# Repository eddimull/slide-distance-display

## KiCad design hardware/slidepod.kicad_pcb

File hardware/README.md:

# SlidePod: wireless trombone slide sensor

A single clip-on pod for the stationary inner slide. It measures slide extension with a
VL53L1X time-of-flight sensor and pitch with a piezo contact pickup. It sends position,
pitch and partial over BLE to the Flutter app. There is no screen and no wire to the bell.

## Mechanical constraint that shapes the board

The VL53L1X emits **perpendicular to the PCB**. For the beam to run down the slide, the
board stands as a thin "fin" perpendicular to the slide tubes:

```
        side view (slide runs left → right)

            ┌──┐  ← antenna end (top, away from brass)
            │  │
     PCB →  │  │──►  ToF beam toward the reflector tab on the outer handle brace
   (fin)    │  │
            │▓▓│  ← battery behind the board
     ═══════╧══╧═════════ inner slide tube (clamp + piezo at bottom)
```

- The ToF sits on the **front face** with nothing taller than it nearby. The ESP32 module,
  USB-C, switch and battery connector go on the back or sides.
- The module antenna sits at the top edge, as far from the brass as possible, with copper
  keep-out on all layers under and around it per the Espressif guidelines.
- The piezo disc is in the clamp and connects to two pads at the bottom edge.

Current outline: **30 × 50 mm**, 4-layer, 1.0 mm thick, single-sided assembly. It can shrink later by moving parts to the back side, but JLC charges more for double-sided assembly.

## Block diagram

```
USB-C ─ESD─┬─ D+/D- ──────────────────────────────► ESP32-S3 GPIO19/20 (native USB)
           └─ VBUS ─┬─► MCP73831 ──► VBAT ─┐
                    │                       ├─(power path)─► SW ─► VSYS ─► ME6211 ─► 3V3
                    └──────── Schottky ─────┘   P-FET from VBAT, gated by VBUS
JST-PH (1S LiPo with protection PCB) ─► VBAT

3V3 ─► ESP32-S3-MINI-1, VL53L1X, MCP6001, status LEDs
```

## Pin map (ESP32-S3-MINI-1)

| Net | GPIO | Notes |
|---|---|---|
| PIEZO_ADC | 1 | ADC1_CH0, continuous/DMA mode at 8–16 kHz |
| VBAT_SENSE | 2 | ADC1_CH1, 1M/1M divider from VBAT + 100 nF (about 2 µA drain) |
| TOF_INT | 4 | VL53L1X GPIO1 (open-drain, 10k pull-up) |
| TOF_XSHUT | 5 | 10k pull-up; drive low to power the sensor down |
| I2C_SDA | 8 | 4.7k pull-up |
| I2C_SCL | 9 | 4.7k pull-up |
| VBUS_SENSE | 10 | 100k/100k divider from VBUS (5 V → 2.5 V): USB present |
| LED_R / LED_G / LED_B | 11 / 12 / 13 | Three 0603 LEDs, anodes to 3V3, active-low, LEDC PWM |
| USB_D- / USB_D+ | 19 / 20 | Built-in USB-Serial/JTAG for flashing and logs |
| BOOT | 0 | Tactile switch to GND, 10k pull-up |
| EN | EN | 10k pull-up + 1 µF to GND, RESET switch to GND |
| U0TXD / U0RXD | 43 / 44 | Test pads only |

Avoided: strapping pins 3, 45, 46, and ADC2, which conflicts with the radio.

**Why discrete LEDs and not a WS2812:** the system runs at 3.3 V, below the WS2812's
rated supply. A WS2812 also draws about 1 mA even when off, while discrete LEDs on LEDC
draw nothing.

## Circuit blocks

### Power
- **USB-C receptacle (16-pin):** CC1 and CC2 each get 5.1k to GND (UFP, 5 V default).
  USBLC6-2SC6 on D+/D-/VBUS.
- **MCP73831T-2ACI/OT charger:** 4.2 V. R_PROG = 3.3k sets I_chg = 1000 V / 3.3 kΩ ≈ 300 mA
  (about 0.75C for a 400 mAh cell). 4.7 µF on VBUS and on VBAT.
- **Power path:** a Schottky diode from VBUS feeds VSYS. A P-MOSFET (gate to VBUS, 100k
  gate pull-down) connects VBAT to VSYS when USB is absent. This way the charger never
  sees the system load.
- **Power switch:** an SMD slide switch in series with VSYS. The battery still charges with the switch off.
- **Charge LED:** an orange LED on MCP73831 STAT (lit while charging). STAT is not wired to the ESP32, so an unpowered ESP32 is never back-fed through it.
- **ME6211C33 LDO:** 500 mA, enough for ESP32-S3 radio peaks of about 350 mA. 10 µF in and 10 µF out.
- **Battery:** 1S LiPo, 300–500 mAh, **with a protection PCB** (this board doesn't add protection).

### ESP32-S3-MINI-1
- 3V3 on all supply pins, with 10 µF + 100 nF near the module, plus 100 nF at each supply pin group.
- All GND pads go to a solid ground plane on layer 2, stitched with vias.

### VL53L1X
- AVDD and AVDDVCSEL to 3V3, each with 100 nF, plus 4.7 µF bulk.
- I2C address 0x29. XSHUT and GPIO1 as in the pin map.
- Enclosure: an open aperture in front of the sensor, or an IR-transparent cover window
  spaced per ST AN4907. Run crosstalk calibration in firmware if there's a cover.

### Piezo front end (MCP6001)
```
3V3 ─100k─┬─100k─ GND          Vb = mid-rail, 10 µF to GND
          Vb
          │
         1M 
          │
PIEZO+ ──┼──1k──► (+) MCP6001 ──┬── out ──1k──┬──► PIEZO_ADC (GPIO1)
PIEZO- ──GND  BAT54S to 3V3/GND  │              10 nF
                          (−) ─┬─ Rf 100k (DNP-able 47k option)
                               Rg 10k ── 1 µF ── Vb
```
- Gain is about 11, and there are footprints for a second Rf value because gain is the main unknown.
- The high-pass corner (10 MΩ with the piezo's C) is well under 40 Hz. Real band-limiting
  (about 35 Hz to 2 kHz) happens in firmware.
- The 1k/10 nF RC is the anti-alias filter (fc ≈ 16 kHz) and isolates the ADC sampling cap.

### Indicator and controls
- Three separate 0603 LEDs (red, green, blue), side by side for a light pipe. Series resistors: 1k red (about 1.3 mA), 33 Ω green and blue (about 3–9 mA, depending on Vf at 3.3 V). Balance brightness with PWM in firmware.
  A combined RGB package was dropped because no JLC common-anode part had a pinout I could verify.
- BOOT and RESET tactile switches on the board edge, which the enclosure can expose as pinholes.

### Test points
3V3, VSYS, VBAT, GND, PIEZO_ADC, U0TXD, U0RXD.

## Key parts (JLCPCB / LCSC)

Check live stock and the Basic/Extended label on jlcpcb.com/partdetail/<C#> before ordering.

| Ref | Part | LCSC | Status |
|---|---|---|---|
| U1 | ESP32-S3-MINI-1-N8 | C2913206 | Extended. Alternate: N4R2 C3013941 (PSRAM, not needed) |
| U2 | VL53L1CXV0FY/1 | C190004 | Not yet confirmed on JLC |
| U3 | MCP73831T-2ACI/OT | C424093 | Not yet confirmed |
| U4 | ME6211C33M5G-N | C82942 | Extended. Alternate: AP2112K-3.3 C51118 |
| U5 | MCP6001T-I/OT | C116490 | Not yet confirmed |
| U6 | USBLC6-2SC6 (ST) | C7519 | Extended |
| J1 | TYPE-C-31-M-12 | C165948 | Extended |
| J2 | JST S2B-PH-SM4-TB | C295747 | Extended |
| D1 | BAT54S (Nexperia) | C47546 | Extended (no Basic BAT54S exists) |
| SW1/2 | TS-1187A-B-A-B | C318884 | Not yet confirmed |
| SW3 | MSK12C02 | C431540 | Not yet confirmed |
| Q1 | AO3401A | C15127 | Basic |
| D2 | B5819W (CJ) | C8598 | Basic |
| LED1, D3 | KT-0603R red | C2286 | Basic |
| LED2 / LED3 | KT-0603G green / KT-0603B blue | C12624 / C2288 | Extended (no Basic green or blue 0603 LEDs at JLC) |
| R, C | 0402 resistors and capacitors (4.7 µF and 10 µF are 0603) | see `LCSC_R0402` / `LCSC_C` in `tools/circuit.py` | Basic |

## Firmware-facing summary
- I2C @ 400 kHz on GPIO8/9. VL53L1X in Short mode, 20 ms budget, 8×8 ROI.
- Piezo on ADC1_CH0, continuous mode.
- BLE GATT notify at 50 Hz with about 10 bytes per update. Calibration (offset, length) goes in a writable characteristic.

## Design files and workflow

The schematic and board are **generated** from Python, so changes are reviewable as code:

| File | Role |
|---|---|
| `tools/circuit.py` | **Source of truth:** parts, values, footprints, LCSC numbers, pin-to-net map |
| `tools/gen_sch.py` | Builds `slidepod.kicad_sch` (a net label on every pin, using KiCad library symbols) |
| `tools/gen_pcb.py` | Builds `slidepod.kicad_pcb`: outline, 4-layer stackup, net classes, placement, GND pours |
| `tools/check_net.py` | Checks the exported netlist against `circuit.py`, pin by pin |
| `tools/kicad.sh` | Runs any command in the `kicad/kicad:9.0` Docker image (no local install needed) |

```sh
make            # ERC, netlist check against circuit.py, DRC with schematic parity
make pcb        # re-place the board (DISCARDS routing; use only before routing)
make route      # fan-out, Freerouting, finish, stitch (about 30 min)
make fab        # Gerbers, drill, BOM, CPL into fab/
make pdf        # schematic PDF
```

**Placement:** anchor parts (module, ToF, connectors, buttons, LED) have fixed positions
in `ANCHORS`. Everything else is packed to the nearest free spot beside the pins it
connects to. Parts excluded from placement:

- the antenna band (top 6.6 mm), via the module's keep-out rule area
- a 6 × 3.8 mm window around the VL53L1X

### Status (rev 0.1)
- [x] Schematic: ERC clean, netlist matches `circuit.py` (233 pins)
- [x] Board: 30 × 50 mm, 4 layers. Placement, routing, GND/+3V3 planes, stitching.
      **DRC: 0 errors, 0 unconnected, schematic parity clean.**
- [x] Fab outputs in `fab/`: `slidepod-gerbers.zip` (Gerbers + drill), `slidepod-bom.csv`, `slidepod-cpl.csv`
- [x] LCSC numbers on every BOM line
- [ ] Recheck the MCP6001, VL53L1X, MCP73831 and switches on JLC
- [ ] In JLC's assembly preview, check every part's rotation (CPL rotations follow KiCad's zero orientation)

### Stackup and routing pipeline (`make route`)

| Layer | Use |
|---|---|
| F.Cu | Signals + GND pour |
| In1.Cu | Solid GND plane |
| In2.Cu | +3V3 plane |
| B.Cu | Signals + GND pour |

1. `stitch.py fanout`: every +3V3 and GND pad gets a via to its plane plus a short stub, all locked.
2. Freerouting (headless, `.tools/freerouting.jar`) routes the signal nets. GND is excluded.
3. `route.py import` brings the routes back into KiCad.
4. `finish_route.py`: a small grid A* router connects whatever Freerouting left open.
5. `stitch.py finish` removes dangling stubs, adds a 3 mm grid of GND stitching vias, and refills the pours.

`move_part.py REF TARGET PAD` moves one part on the routed board and re-routes its nets
with `finish_route.py`. Rev 0.1 used it once: R6 went next to R7 and C5, so the whole
battery-sense divider sits at the ADC pin. `gen_pcb.py` now places it there itself.

### Review before ordering
- The piezo amplifier gain (R23, with R24 left unfitted) is a guess. Test it on a real horn.
- The JST-PH battery polarity isn't standard across vendors. Check the battery leads against the `+` marking.
- The VL53L1X needs an open aperture or a proper cover window in the enclosure (ST AN4907).
- Check BLE range with the pod clamped on the horn. Brass near the antenna detunes it.
- A few F.Cu traces run under the ESP32 module, between its center GND pads (solder mask covers them). Espressif allows this outside the antenna area, but rerouting them would remove any risk of shorts.

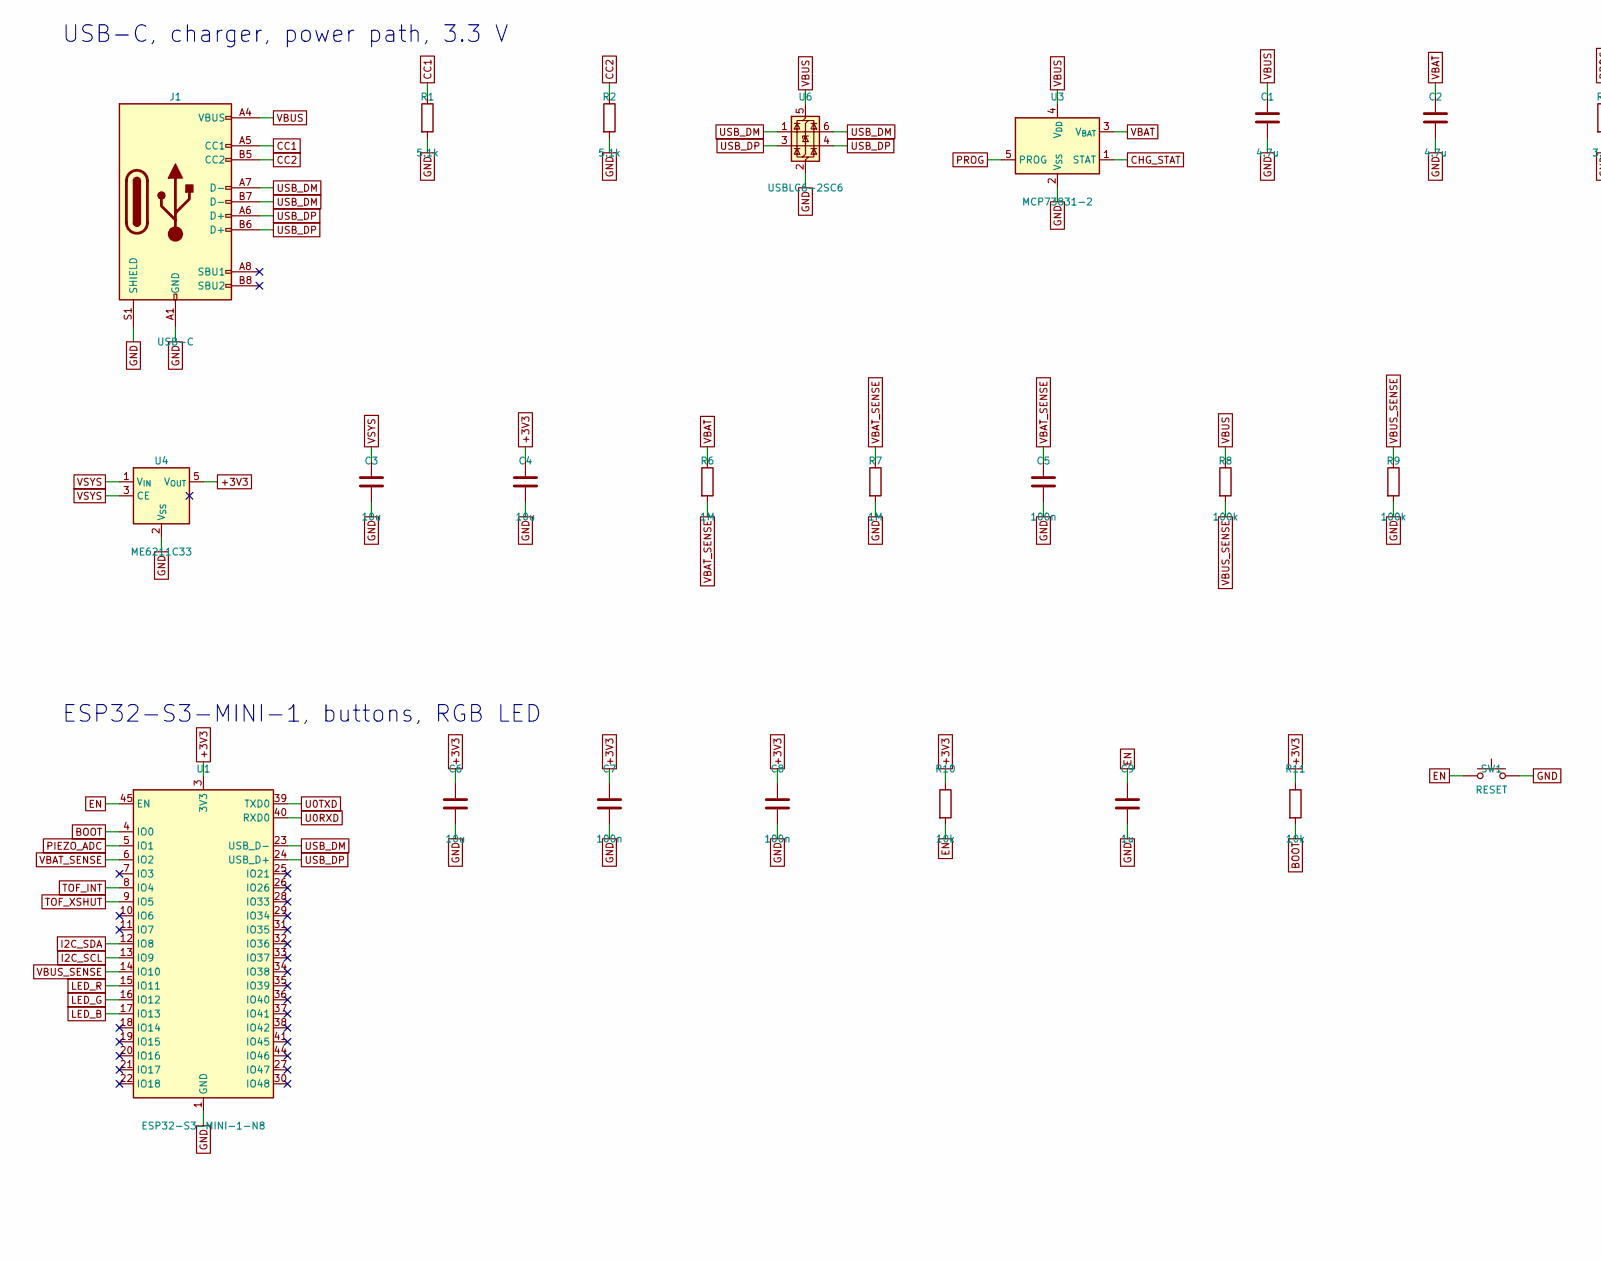
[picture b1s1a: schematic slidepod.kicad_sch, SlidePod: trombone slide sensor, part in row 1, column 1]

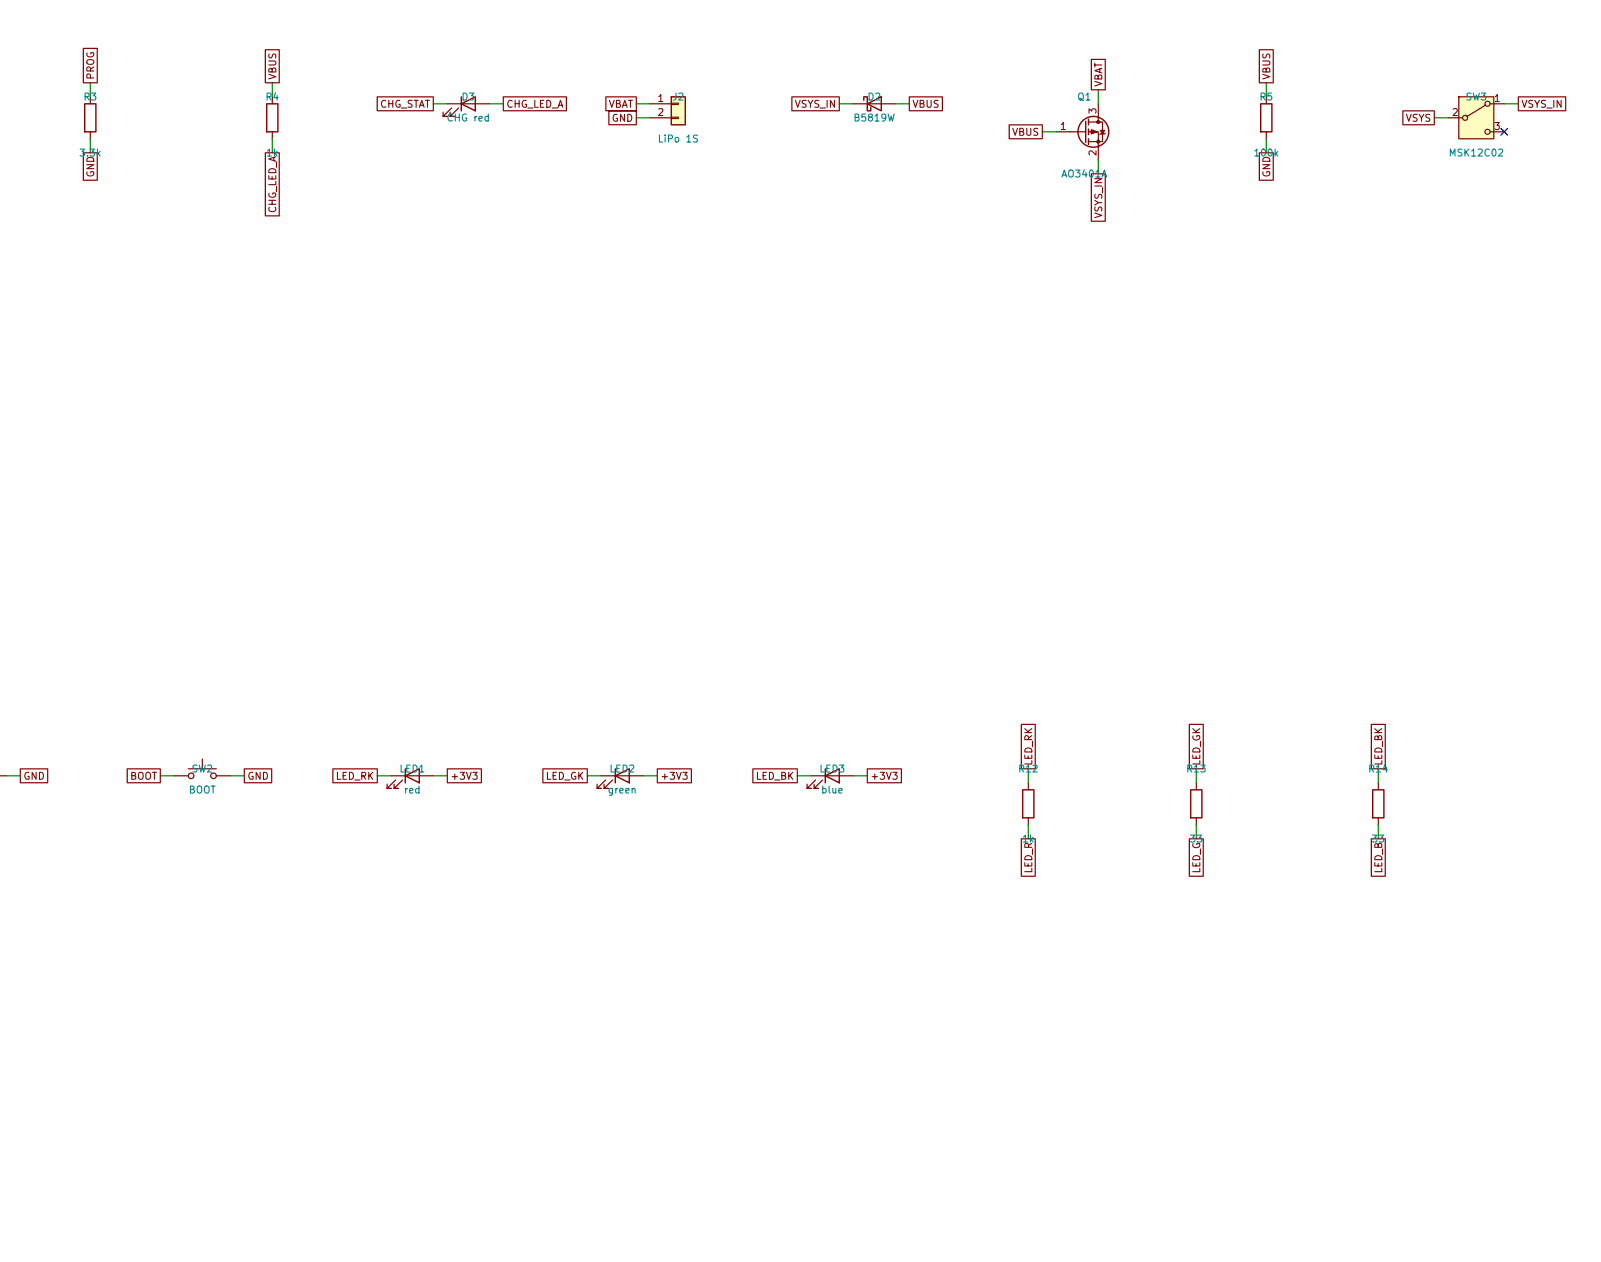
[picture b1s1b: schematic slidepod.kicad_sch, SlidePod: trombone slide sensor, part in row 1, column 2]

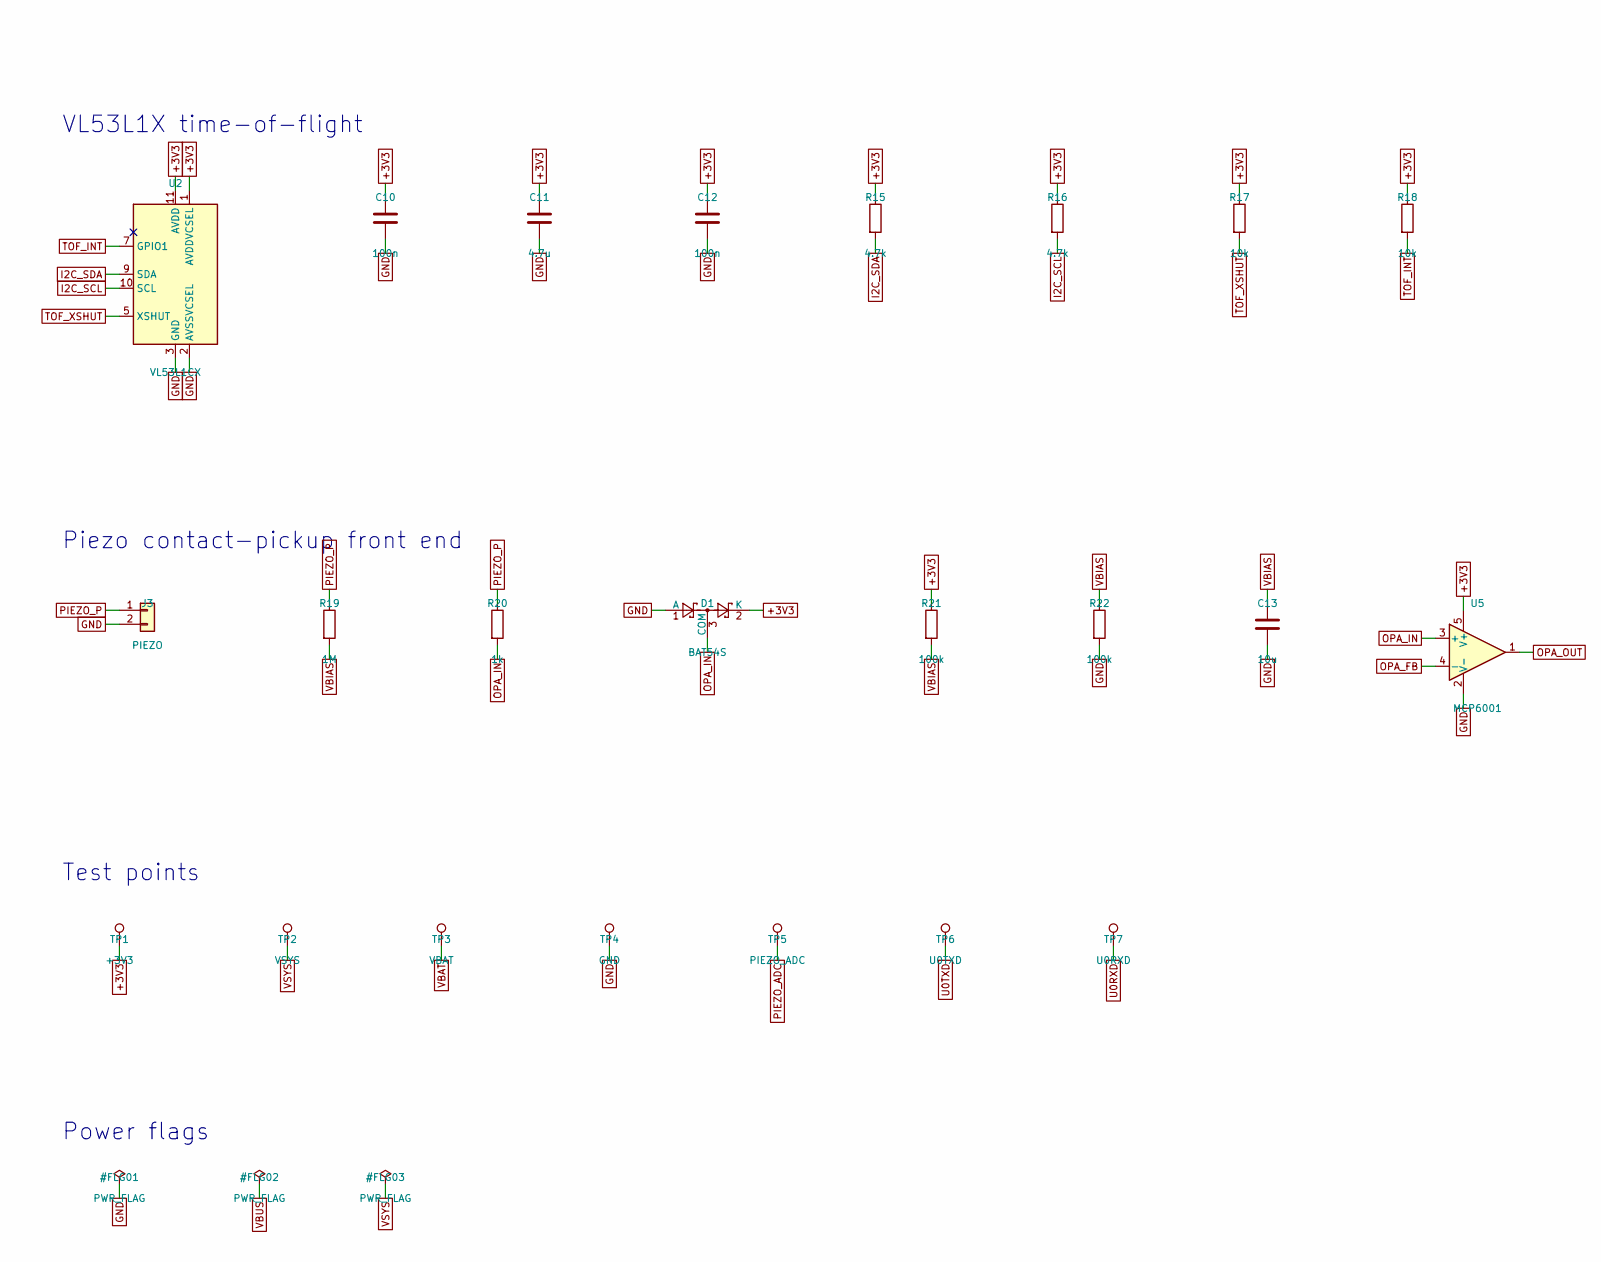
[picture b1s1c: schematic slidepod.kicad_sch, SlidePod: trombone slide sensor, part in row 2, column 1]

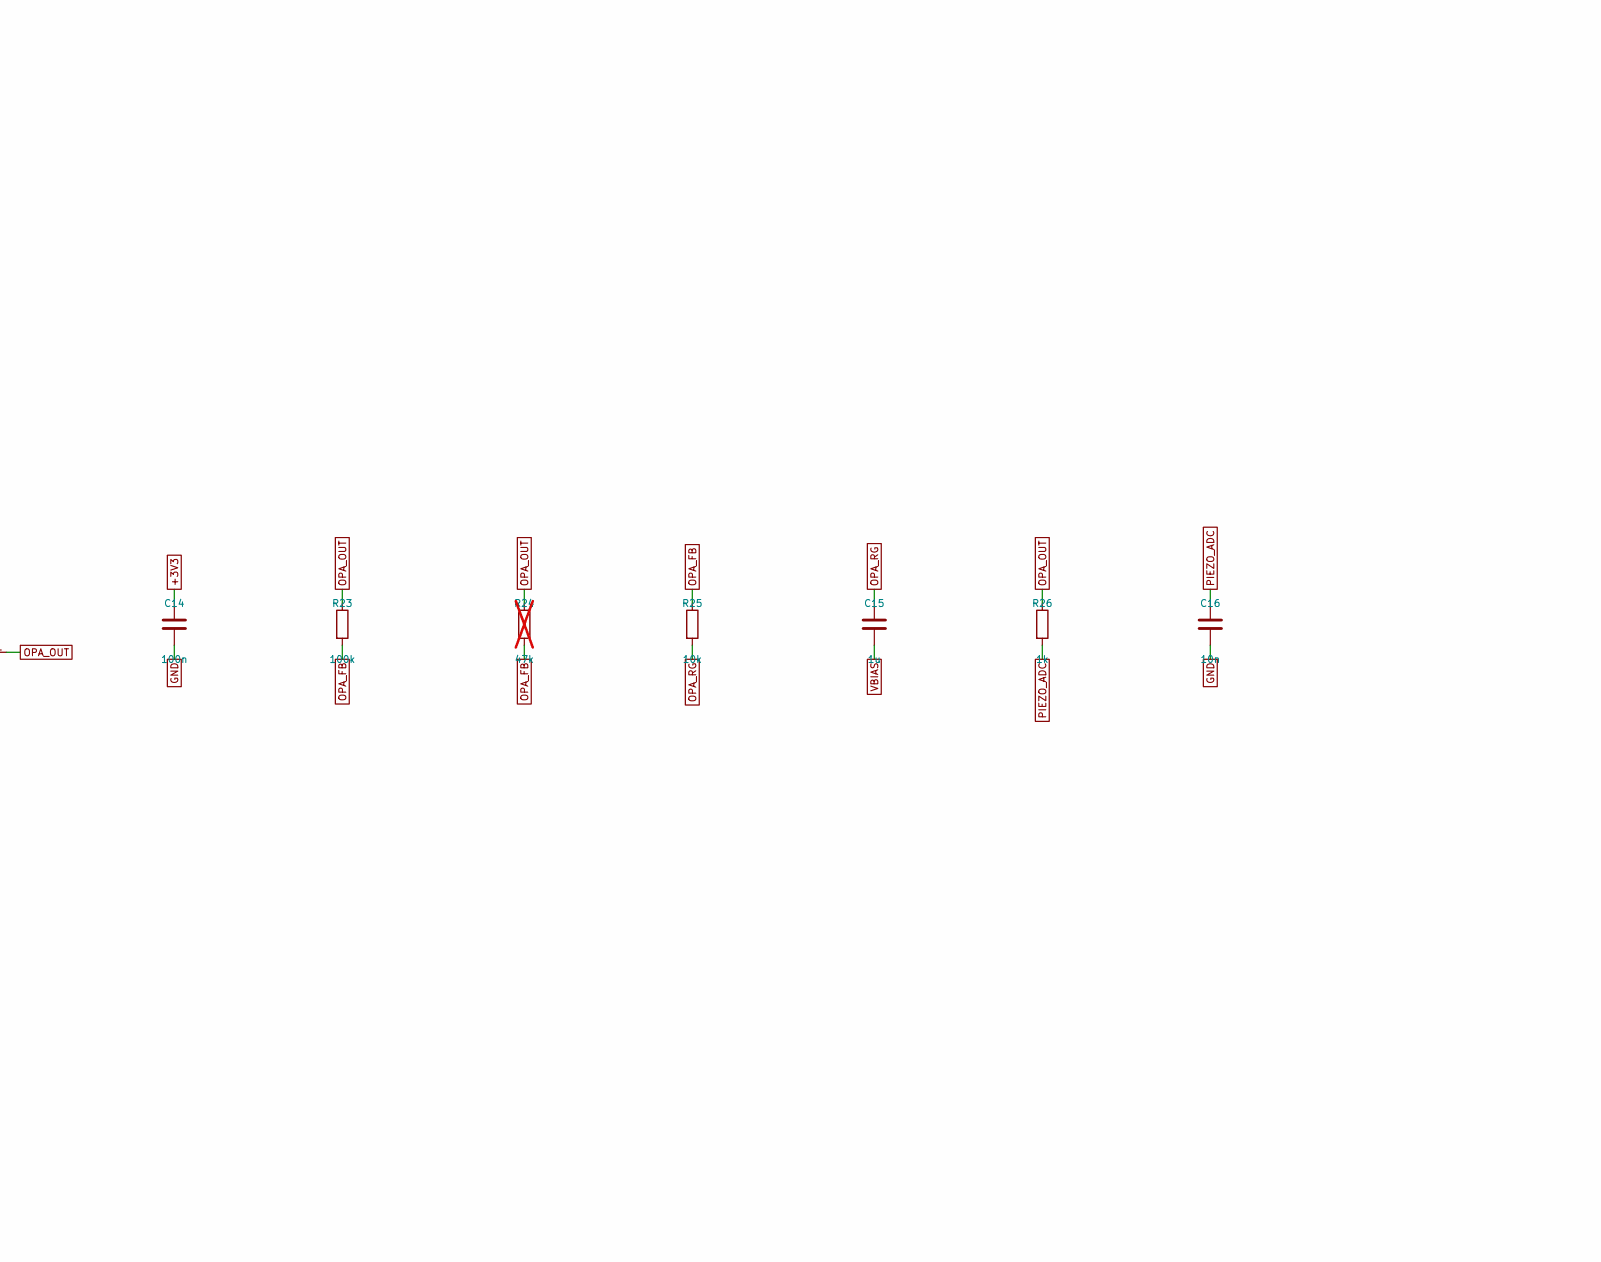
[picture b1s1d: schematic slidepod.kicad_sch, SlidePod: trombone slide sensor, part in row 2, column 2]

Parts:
C1, C2, C11: 4.7u; C_0603_1608Metric; LCSC C19666
C3, C4, C6, C13: 10u; C_0603_1608Metric; LCSC C19702
C5, C7, C8, C10, C12, C14: 100n; C_0402_1005Metric; LCSC C1525
C9, C15: 1u; C_0402_1005Metric; LCSC C52923
C16: 10n; C_0402_1005Metric; LCSC C15195
D1: BAT54S; SOT-23; LCSC C47546
D2: B5819W; D_SOD-123; LCSC C8598
D3: CHG red; LED_0603_1608Metric; LCSC C2286
J1: USB-C; USB_C_Receptacle_HRO_TYPE-C-31-M-12; LCSC C165948
J2: LiPo 1S; JST_PH_S2B-PH-SM4-TB_1x02-1MP_P2.00mm_Horizontal; LCSC C295747
J3: PIEZO; SolderWire-0.1sqmm_1x02_P3.6mm_D0.4mm_OD1mm
LED1: red; LED_0603_1608Metric; LCSC C2286
LED2: green; LED_0603_1608Metric; LCSC C12624
LED3: blue; LED_0603_1608Metric; LCSC C2288
Q1: AO3401A; SOT-23; LCSC C15127
R1, R2: 5.1k; R_0402_1005Metric; LCSC C25905
R3: 3.3k; R_0402_1005Metric; LCSC C25890
R4, R12, R20, R26: 1k; R_0402_1005Metric; LCSC C11702
R5, R8, R9, R21, R22, R23: 100k; R_0402_1005Metric; LCSC C25741
R6, R7, R19: 1M; R_0402_1005Metric; LCSC C26083
R10, R11, R17, R18, R25: 10k; R_0402_1005Metric; LCSC C25744
R13, R14: 33; R_0402_1005Metric; LCSC C25105
R15, R16: 4.7k; R_0402_1005Metric; LCSC C25900
R24: 47k; R_0402_1005Metric; LCSC C25792; not fitted
SW1: RESET; SW_Push_1P1T_XKB_TS-1187A; LCSC C318884
SW2: BOOT; SW_Push_1P1T_XKB_TS-1187A; LCSC C318884
SW3: MSK12C02; SW_SPDT_Shouhan_MSK12C02; LCSC C431540
TP1: +3V3; TestPoint_Pad_D1.0mm
TP2: VSYS; TestPoint_Pad_D1.0mm
TP3: VBAT; TestPoint_Pad_D1.0mm
TP4: GND; TestPoint_Pad_D1.0mm
TP5: PIEZO_ADC; TestPoint_Pad_D1.0mm
TP6: U0TXD; TestPoint_Pad_D1.0mm
TP7: U0RXD; TestPoint_Pad_D1.0mm
U1: ESP32-S3-MINI-1-N8; ESP32-S2-MINI-1; LCSC C2913206
U2: VL53L1CX; ST_VL53L1x; LCSC C190004
U3: MCP73831-2; SOT-23-5; LCSC C424093
U4: ME6211C33; SOT-23-5; LCSC C82942
U5: MCP6001; SOT-23-5; LCSC C116490
U6: USBLC6-2SC6; SOT-23-6; LCSC C7519

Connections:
+3V3: C4.1, C6.1, C7.1, C8.1, C10.1, C11.1, C12.1, C14.1, D1.2 (K), LED1.2 (A), LED2.2 (A), LED3.2 (A), R10.1, R11.1, R15.1, R16.1, R17.1, R18.1, R21.1, TP1.1, U1.3 (3V3), U2.1 (AVDDVCSEL), U2.11 (AVDD), U4.5 (V_{OUT}), U5.5 (V+)
BOOT: R11.2, SW2.1, U1.4 (IO0)
CC1: J1.A5 (CC1), R1.1
CC2: J1.B5 (CC2), R2.1
CHG_LED_A: D3.2 (A), R4.2
CHG_STAT: D3.1 (K), U3.1 (STAT)
EN: C9.1, R10.2, SW1.1, U1.45 (EN)
GND: C1.2, C2.2, C3.2, C4.2, C5.2, C6.2, C7.2, C8.2, C9.2, C10.2, C11.2, C12.2, C13.2, C14.2, C16.2, D1.1 (A), J1.A1 (GND), J1.A12 (GND), J1.B1 (GND), J1.B12 (GND), J1.S1 (SHIELD), J2.2, J3.2, R1.2, R2.2, R3.2, R5.2, R7.2, R9.2, R22.2, SW1.2, SW2.2, TP4.1, U1.1 (GND), U1.2 (GND), U1.42 (GND), U1.43 (GND), U1.46 (GND), U1.47 (GND), U1.48 (GND), U1.49 (GND), U1.50 (GND), U1.51 (GND), U1.52 (GND), U1.53 (GND), U1.54 (GND), U1.55 (GND), U1.56 (GND), U1.57 (GND), U1.58 (GND), U1.59 (GND), U1.60 (GND), U1.61 (GND), U1.62 (GND), U1.63 (GND), U1.64 (GND), U1.65 (GND), U2.2 (AVSSVCSEL), U2.3 (GND), U2.4 (GND), U2.6 (GND), U2.12 (GND), U3.2 (V_{SS}), U4.2 (V_{SS}), U5.2 (V-), U6.2 (GND)
I2C_SCL: R16.2, U1.13 (IO9), U2.10 (SCL)
I2C_SDA: R15.2, U1.12 (IO8), U2.9 (SDA)
LED_B: R14.2, U1.17 (IO13)
LED_BK: LED3.1 (K), R14.1
LED_G: R13.2, U1.16 (IO12)
LED_GK: LED2.1 (K), R13.1
LED_R: R12.2, U1.15 (IO11)
LED_RK: LED1.1 (K), R12.1
OPA_FB: R23.2, R24.2, R25.1, U5.4 (-)
OPA_IN: D1.3 (COM), R20.2, U5.3 (+)
OPA_OUT: R23.1, R24.1, R26.1, U5.1
OPA_RG: C15.1, R25.2
PIEZO_ADC: C16.1, R26.2, TP5.1, U1.5 (IO1)
PIEZO_P: J3.1, R19.1, R20.1
PROG: R3.1, U3.5 (PROG)
TOF_INT: R18.2, U1.8 (IO4), U2.7 (GPIO1)
TOF_XSHUT: R17.2, U1.9 (IO5), U2.5 (XSHUT)
U0RXD: TP7.1, U1.40 (RXD0)
U0TXD: TP6.1, U1.39 (TXD0)
USB_DM: J1.A7 (D-), J1.B7 (D-), U1.23 (USB_D-), U6.1 (I/O1), U6.6 (I/O1)
USB_DP: J1.A6 (D+), J1.B6 (D+), U1.24 (USB_D+), U6.3 (I/O2), U6.4 (I/O2)
VBAT: C2.1, J2.1, Q1.3 (D), R6.1, TP3.1, U3.3 (V_{BAT})
VBAT_SENSE: C5.1, R6.2, R7.1, U1.6 (IO2)
VBIAS: C13.1, C15.2, R19.2, R21.2, R22.1
VBUS: C1.1, D2.2 (A), J1.A4 (VBUS), J1.A9 (VBUS), J1.B4 (VBUS), J1.B9 (VBUS), Q1.1 (G), R4.1, R5.1, R8.1, U3.4 (V_{DD}), U6.5 (VBUS)
VBUS_SENSE: R8.2, R9.1, U1.14 (IO10)
VSYS: C3.1, SW3.2 (B), TP2.1, U4.1 (V_{IN}), U4.3 (CE)
VSYS_IN: D2.1 (K), Q1.2 (S), SW3.1 (A)

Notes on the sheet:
USB-C, charger, power path, 3.3 V
ESP32-S3-MINI-1, buttons, RGB LED
VL53L1X time-of-flight
Piezo contact-pickup front end
Test points
Power flags

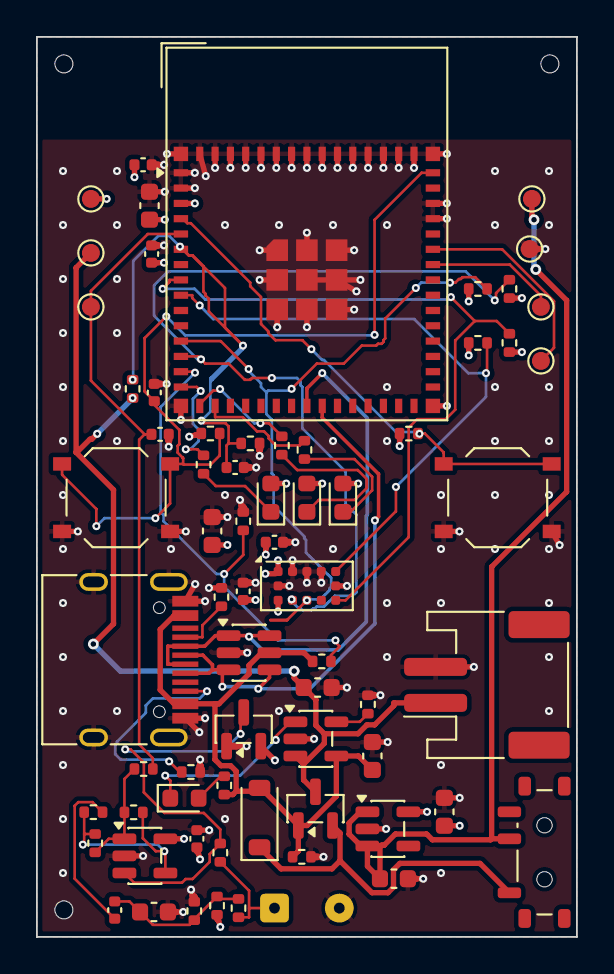
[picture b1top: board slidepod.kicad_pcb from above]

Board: 4 copper layers, 30.0 x 50.0 mm, 71 parts (0 on the bottom side), 36 nets.

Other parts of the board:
TH1, TH2, TH3: (no value)

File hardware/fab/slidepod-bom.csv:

Comment,Designator,Footprint,LCSC Part #
4.7u,"C1,C11,C2",C_0603_1608Metric,C19666
100n,"C10,C12,C14,C5,C7,C8",C_0402_1005Metric,C1525
10u,"C13,C3,C4,C6",C_0603_1608Metric,C19702
1u,"C15,C9",C_0402_1005Metric,C52923
10n,C16,C_0402_1005Metric,C15195
BAT54S,D1,SOT-23,C47546
B5819W,D2,D_SOD-123,C8598
CHG red,D3,LED_0603_1608Metric,C2286
USB-C,J1,USB_C_Receptacle_HRO_TYPE-C-31-M-12,C165948
LiPo 1S,J2,JST_PH_S2B-PH-SM4-TB_1x02-1MP_P2.00mm_Horizontal,C295747
red,LED1,LED_0603_1608Metric,C2286
green,LED2,LED_0603_1608Metric,C12624
blue,LED3,LED_0603_1608Metric,C2288
AO3401A,Q1,SOT-23,C15127
5.1k,"R1,R2",R_0402_1005Metric,C25905
10k,"R10,R11,R17,R18,R25",R_0402_1005Metric,C25744
1k,"R12,R20,R26,R4",R_0402_1005Metric,C11702
33,"R13,R14",R_0402_1005Metric,C25105
4.7k,"R15,R16",R_0402_1005Metric,C25900
1M,"R19,R6,R7",R_0402_1005Metric,C26083
100k,"R21,R22,R23,R5,R8,R9",R_0402_1005Metric,C25741
3.3k,R3,R_0402_1005Metric,C25890
RESET,SW1,SW_Push_1P1T_XKB_TS-1187A,C318884
BOOT,SW2,SW_Push_1P1T_XKB_TS-1187A,C318884
MSK12C02,SW3,SW_SPDT_Shouhan_MSK12C02,C431540
ESP32-S3-MINI-1-N8,U1,ESP32-S2-MINI-1,C2913206
VL53L1CX,U2,ST_VL53L1x,C190004
MCP73831-2,U3,SOT-23-5,C424093
ME6211C33,U4,SOT-23-5,C82942
MCP6001,U5,SOT-23-5,C116490
USBLC6-2SC6,U6,SOT-23-6,C7519

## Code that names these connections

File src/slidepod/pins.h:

#pragma once
// SlidePod rev 0.1 pin map (hardware/README.md, hardware/tools/circuit.py).

constexpr int PIN_PIEZO_ADC = 1;    // ADC1_CH0: MCP6001 output, mid-rail biased
constexpr int PIN_VBAT_SENSE = 2;   // ADC1_CH1: VBAT / 2 (1M/1M)
constexpr int PIN_TOF_INT = 4;      // VL53L1X GPIO1, open-drain, active low
constexpr int PIN_TOF_XSHUT = 5;    // VL53L1X shutdown, low = off
constexpr int PIN_I2C_SDA = 8;
constexpr int PIN_I2C_SCL = 9;
constexpr int PIN_VBUS_SENSE = 10;  // ADC1_CH9: VBUS / 2 (100k/100k)
constexpr int PIN_LED_R = 11;       // LEDs: anode to 3V3, GPIO sinks (active low)
constexpr int PIN_LED_G = 12;
constexpr int PIN_LED_B = 13;
constexpr int PIN_BOOT = 0;

// ADC1 channel numbers of the analog pins above (ESP32-S3: GPIOn -> ADC1_CH(n-1)).
constexpr int ADC_CH_PIEZO = 0;
constexpr int ADC_CH_VBAT = 1;
constexpr int ADC_CH_VBUS = 9;

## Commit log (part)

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2024-03-16 init commit
2024-03-17 made the color rectangle sprite. Flickering screen still
2024-03-17 went with my own ultrasonic class
2024-03-20 pausing getting the mic to work
2024-03-20 Got it working.
2024-03-24 added error message on startup
2024-03-24 created a screen state manager color rectangle to render to it
2024-05-25 brought in a kalman filter and got the color sprite to work with it
2024-05-27 cleaned up a little bit and added debug messages
2024-05-27 fixed the velocity cal
2024-05-27 added a fill screen to prevent any extra noise
